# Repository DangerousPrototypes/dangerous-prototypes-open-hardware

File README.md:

# dangerous-prototypes-open-hardware
Automatically exported from code.google.com/p/dangerous-prototypes-open-hardware

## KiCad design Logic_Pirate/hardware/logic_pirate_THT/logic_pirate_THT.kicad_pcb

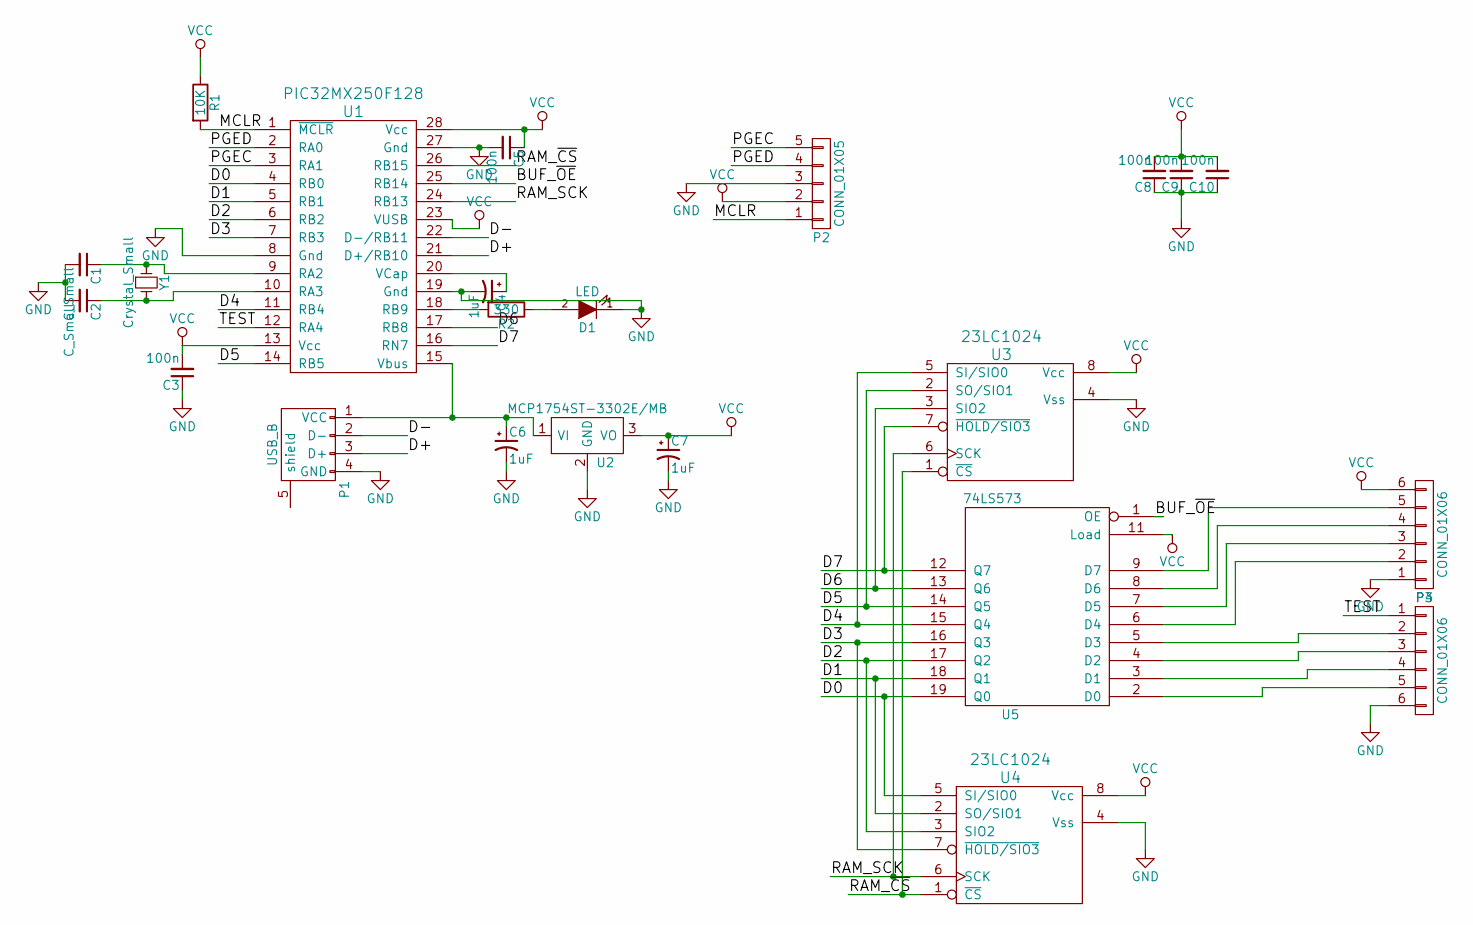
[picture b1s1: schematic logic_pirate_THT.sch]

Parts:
C1, C2: C_Small; C_Disc_D3_P2.5
C3, C5, C8, C9, C10: 100n; C_Disc_D3_P2.5
C4, C6, C7: 1uF; C_Radial_D5_L6_P2.5
D1: LED; LED-5MM
P1: USB_B
P2: CONN_01X05; Pin_Header_Straight_1x05
P3, P4: CONN_01X06; Pin_Header_Straight_1x06
R1: 10K; Resistor_Horizontal_RM10mm
R2: 330; Resistor_Horizontal_RM10mm
U1: PIC32MX250F128; DIP-28_W7.62mm_LongPads
U2: MCP1754ST-3302E/MB; TO-220
U3, U4: 23LC1024; DIP-8_W7.62mm_LongPads
U5: 74LS573; DIP-20_W7.62mm_LongPads
Y1: Crystal_Small; Crystal_HC50-U_Vertical

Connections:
/BUF_~OE: U1.25 (RB14), U5.1 (OE)
/D0: U1.4 (RB0), U4.5 (SI/SIO0), U5.19 (Q0)
/D1: U1.5 (RB1), U4.2 (SO/SIO1), U5.18 (Q1)
/D2: U1.6 (RB2), U4.3 (SIO2), U5.17 (Q2)
/D3: U1.7 (RB3), U4.7 (~HOLD/SIO3), U5.16 (Q3)
/D4: U1.11 (RB4), U3.5 (SI/SIO0), U5.15 (Q4)
/D5: U1.14 (RB5), U3.2 (SO/SIO1), U5.14 (Q5)
/D6: U1.17 (RB8), U3.3 (SIO2), U5.13 (Q6)
/D7: U1.16 (RN7), U3.7 (~HOLD/SIO3), U5.12 (Q7)
/D+: P1.3 (D+), U1.21 (D+/RB10)
/D-: P1.2 (D-), U1.22 (D-/RB11)
/MCLR: P2.1, R1.2, U1.1 (~MCLR)
/PGEC: P2.5, U1.3 (RA1)
/PGED: P2.4, U1.2 (RA0)
/RAM_SCK: U1.24 (RB13), U3.6 (SCK), U4.6 (SCK)
/RAM_~CS: U1.26 (RB15), U3.1 (~CS), U4.1 (~CS)
/TEST: P4.1, U1.12 (RA4)
GND: C1.2, C2.2, C3.1, C4.2, C5.2, C6.2, C7.2, C8.1, C9.1, C10.1, D1.1 (K), P1.4 (GND), P2.3, P3.1, P4.6, U1.8 (Gnd), U1.19 (Gnd), U1.27 (Gnd), U2.2 (GND), U3.4 (Vss), U4.4 (Vss), U5.10 (GND)
unnamed: C1.1, U1.9 (RA2), Y1.1
unnamed: C2.1, U1.10 (RA3), Y1.2
unnamed: C4.1, U1.20 (VCap)
unnamed: C6.1, P1.1 (VCC), U1.15 (Vbus), U2.1 (VI)
unnamed: D1.2 (A), R2.1
unnamed: P3.2, U5.6 (D4)
unnamed: P3.3, U5.7 (D5)
unnamed: P3.4, U5.8 (D6)
unnamed: P3.5, U5.9 (D7)
unnamed: P4.2, U5.5 (D3)
unnamed: P4.3, U5.4 (D2)
unnamed: P4.4, U5.3 (D1)
unnamed: P4.5, U5.2 (D0)
unnamed: R2.2, U1.18 (RB9)
VCC: C3.2, C5.1, C7.1, C8.2, C9.2, C10.2, P2.2, P3.6, R1.1, U1.13 (Vcc), U1.23 (VUSB), U1.28 (Vcc), U2.3 (VO), U3.8 (Vcc), U4.8 (Vcc), U5.11 (Load), U5.20 (VCC)

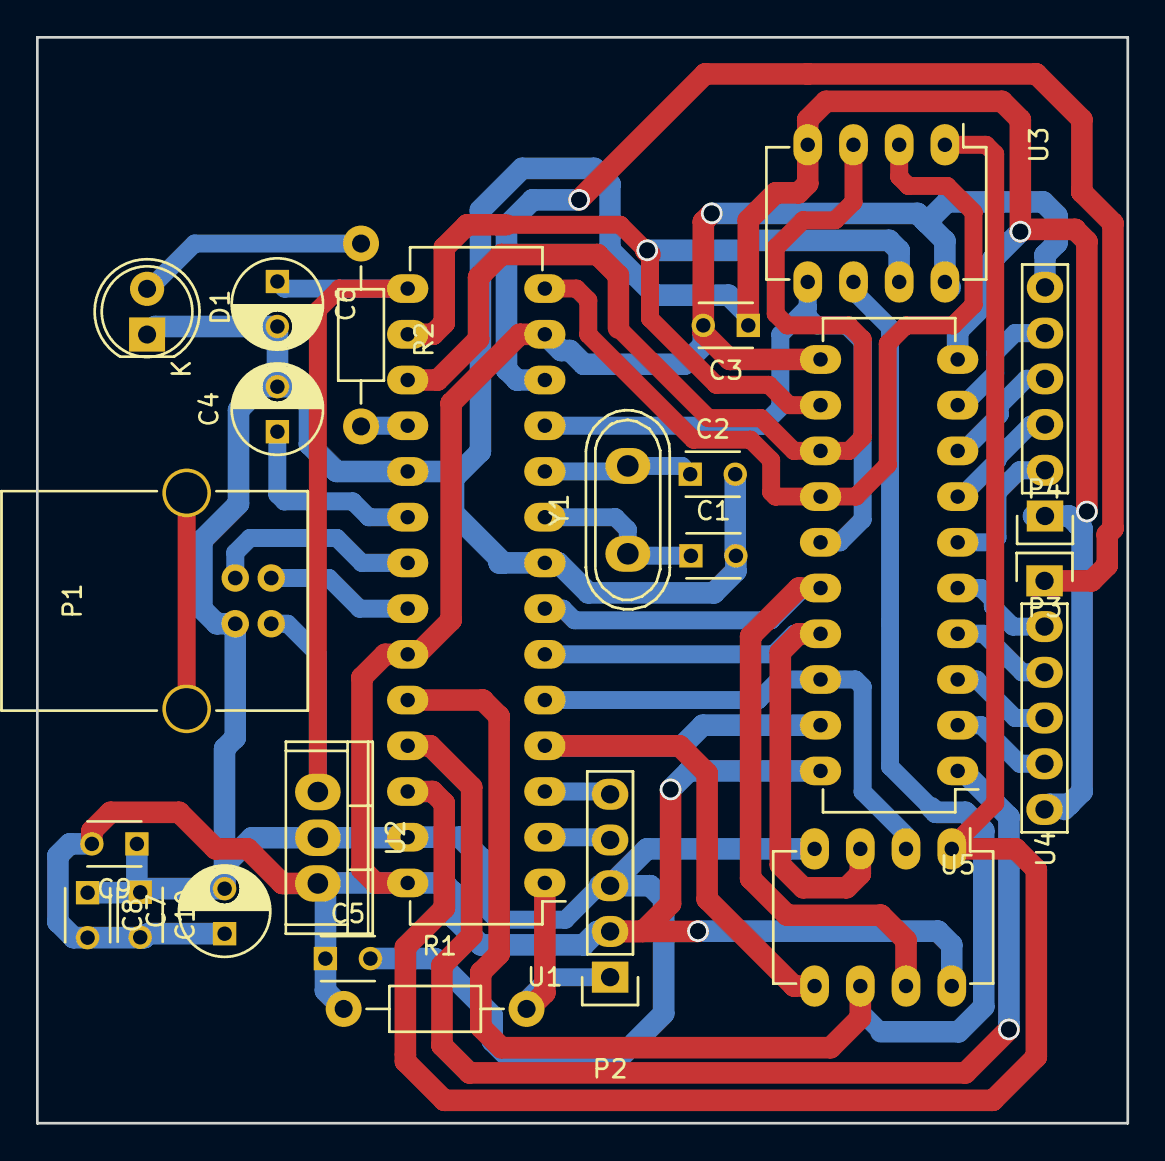
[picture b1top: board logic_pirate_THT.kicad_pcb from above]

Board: 2 copper layers, 60.6 x 60.3 mm, 23 parts (0 on the bottom side), 33 nets.

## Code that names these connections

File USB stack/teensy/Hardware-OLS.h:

/*
*
*	Open Logic Sniffer firmware v1.1
*	http://www.gadgetfactory.net
*	http://dangerousprototypes.com
*	License: GPL
*	Copyright Ian Lesnet 2010
*
*/
#ifndef HARDWARE_PROFILE_H
#define HARDWARE_PROFILE_H

//the first batch of OLS has 20mhz crystal on the PIC
//use this to compile for that hardware
#define XTAL_20MHZ

//hardware version string
#define HW_VER 0x01

//firmware version string
#define FW_VER_H 0x00
#define FW_VER_L 0x06

//Define to enable manufacturing hardware 
//self-test with jumper check on UART header.
//If there is a jumper between RX and TX
//the firmware will light the ACT LED and send 0x03 
//to the FPGA through the UART. THis triggers a test mode
//in special bitstream builds.
#define SELF_TEST	

//measure the voltage on PROG_B (AN3/RA3), should be 2.5volts
#define VREG_TEST
//calculate the ADC value to test for
//#define ADC_2V5 ((25/33)*1024) //2.5volts/3.3volts * 1024 = ADC reading (775.75).
//#define ADC_2V5_LIMIT (ADC_2V5-(ADC_2V5/10)) //show error if not within 10% 775-78=697
#define ADC_2V5_LIMIT 697

//During testing we used a pin for the UART 
// that was sharted with a trigger pin
// some old bitstreams used it and it got confusing
//We had to keep changing it back and forth so I added this define
//There isn't really any reason you should ever need this, 
// especially in the SPI version, but here it is. Enjoy.
//#define OLDRXPIN //use RX on the old pin

//pin setup
/*
A0 PR0 flash_si
A1 PR1 flash_so
A2 flash_cs
A3 PROG_B (pull-down only) test high
A5 RP2 DONE (input only) test high, eventually
C1 RP12 update button (input/interrupt) test high
C2 RP13 ACT LED

B7 RP10 PGD
B6 RP9 PGC
B5 RP8 flash_sck
B4 RP7 FPGA_AUX0
B3 RP6 fpga_cs
B2 RP5 fpga_aux1
B1 RP4 FPGA_AUX2
B0 RP3 FPGA_AUX3
C7 RP18 RX1
C6 RP17 TX1
*/
#define PIN_PROG_B 		PORTAbits.RA3
#define TRIS_PROG_B 	TRISAbits.TRISA3
#define PROG_B_LOW()	PIN_PROG_B=0; TRIS_PROG_B=0 //ground,output
#define PROG_B_HIGH()	PIN_PROG_B=0; TRIS_PROG_B=1	

#define PIN_DONE		PORTAbits.RA5
#define PIN_UPDATE 		PORTCbits.RC1
#define PIN_LED			PORTCbits.RC2

#define TRIS_UART1_TX	TRISCbits.TRISC6
#define PIN_UART1_TX	LATCbits.LATC6
#define TRIS_UART1_RX	TRISCbits.TRISC7
#define PIN_UART1_RX	PORTCbits.RC7
//	#define TRIS_UART1		TRISC
//	#define TXPIN_UART1		0b01000000
//	#define RXPIN_UART1		0b10000000

#define TRIS_UART2_TX	TRISBbits.TRISB1
#define PIN_UART2_TX	PORTBbits.RB1

#define TRIS_FLASH_SCK	TRISBbits.TRISB5
#define PIN_FLASH_SCK	PORTBbits.RB5
#define TRIS_FLASH_MOSI	TRISAbits.TRISA0
#define PIN_FLASH_MOSI	PORTAbits.RA0

#define TRIS_FLASH_CS	TRISAbits.TRISA2
#define PIN_FLASH_CS	PORTAbits.RA2
#define FPGA_CS_LOW()	PIN_FLASH_CS=0; TRIS_FLASH_CS=0
#define FPGA_CS_HIGH() 	PIN_FLASH_CS=1; TRIS_FLASH_CS=0

#define TRIS_FPGA_SCK	TRISBbits.TRISB4
#define PIN_FPGA_SCK	PORTBbits.RB4
#define TRIS_FPGA_MISO	TRISBbits.TRISB2
#define PIN_FPGA_MISO	PORTBbits.RB2
#define TRIS_FPGA_MOSI	TRISBbits.TRISB3
#define PIN_FPGA_MOSI	PORTBbits.RB3
#define TRIS_FPGA_DATAREADY	TRISBbits.TRISB1
#define PIN_FPGA_DATAREADY	PORTBbits.RB1

#define TRIS_FPGA_CS	TRISAbits.TRISA1
#define PIN_FPGA_CS		PORTAbits.RA1

#define BootloaderJump() _asm goto 0x16 _endasm

//these are unneeded, but the stack complains if they're not defined
//#define USE_SELF_POWER_SENSE_IO
#define tris_self_power     TRISCbits.TRISC2    
#define self_power          1

//#define USE_USB_BUS_SENSE_IO
#define tris_usb_bus_sense  TRISCbits.TRISC2    
#define USB_BUS_SENSE       1 

#endif 

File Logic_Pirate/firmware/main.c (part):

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	bool use_trigger;
} config_t;

#define RAM_SCK LATBbits.LATB13
#define SET_RAM_CLOCK_MANUAL ( RPB13Rbits.RPB13R = 0 ) // (PPS) No Connect
#define SET_RAM_CLOCK_REFCLKO ( RPB13Rbits.RPB13R = 7 ) // (PPS) REFCLKO

#define BUF_OE LATBbits.LATB14
#define SET_BUF_ON ( BUF_OE = 0 )
#define SET_BUF_OFF ( BUF_OE = 1 )

#define RAM_CS LATBbits.LATB15
#define SET_RAM_ON ( RAM_CS = 0 )
#define SET_RAM_OFF \
    Nop();          \
    Nop();          \
    Nop();          \
    RAM_CS = 1
// 50 ns nCS hold time.

#define SET_PARALLEL_IN ( TRISB |= 0x01BF )
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    LATBbits.LATB7 = 1;
    uint32_t mask = 1L << ( bit_count - 1 );
    while ( mask != 0 ) {
        RAM_SCK = 0;
        if ( ( data & mask ) != 0 ) {
            LATBbits.LATB0 = 1;
            LATBbits.LATB4 = 1;
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            LATBbits.LATB4 = 0;
        }
        mask >>= 1;
        RAM_SCK = 1;
    }
    RAM_SCK = 0;
    SET_RAM_OFF;
    LATBbits.LATB0 = 0;
    LATBbits.LATB4 = 0;
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    uint32_t nibble_count = 8;
    while ( nibble_count-- > 0 ) {
        const uint8_t nibble = ( data & mask ) >> 28;
        RAM_SCK = 0;
        parallel_write( ( nibble << 4 ) | nibble );
        data <<= 4;
        RAM_SCK = 1;
    }
    RAM_SCK = 0;
    parallel_write( 0x00 );
}

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                               - config->read_count * 2
                               + config->delay_count * 2 ) % 0x1FFFF;
    sqi_write( 0x03000000 | address ); // Read data from memory array beginning at address.
    RAM_SCK = 1; // Dummy Byte
    RAM_SCK = 0;
    RAM_SCK = 1;
    RAM_SCK = 0;
    SET_PARALLEL_IN;

    uint32_t count = config->read_count << 2;
    uint32_t i = 0;
    while ( count > 0 ) {
        --count;
        RAM_SCK = 1;
        USB_In_Buffer[ i++ ] = parallel_read();
        RAM_SCK = 0;
        if ( i >= USB_IN_ENDPOINT_PACKET_SIZE ) {
            i = 0;
            putUSBUSART( USB_In_Buffer, USB_IN_ENDPOINT_PACKET_SIZE );
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    OC4RS = PBCLK / 1000 * 3 / 4; // 75 % duty cycle.
    RPA4Rbits.RPA4R = 5; // (PPS) OC4

    // RAM_SCK pin
    RPB13Rbits.RPB13R = 7; // (PPS) REFCLKO
    REFOCONbits.RODIV = 1; // SYSCLK / ( 2 * 1 ) MHz
    //REFOCONbits.DIVSWEN = 1;
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    SET_RAM_CLOCK_MANUAL;

    // IO
    TRISBbits.TRISB13 = 0; // RAM_SCK
    RAM_SCK = 0;
    TRISBbits.TRISB14 = 0; // BUF_OE
    SET_BUF_OFF;
    TRISBbits.TRISB15 = 0; // RAM_CS
    SET_RAM_OFF;

    SET_PARALLEL_IN;
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
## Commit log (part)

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2012-08-14 Changes to USB interrupt from JTR
2012-08-14 small fix to BPv4 bootloader (comment in wrong place)
    http://dangerousprototypes.com/forum/viewtopic.php?f=28&t=3441&start=45#p42466
2012-08-14 Added USB interrupt fix to BPv4 from: http://dangerousprototypes.com/forum/viewtopic.php?f=28&t=3441&start=45#p42038
2012-08-16 Bus Pirate Demo board firmware
2012-08-20 Added device: 23LC1024 SRAM in SOIC-8
2012-08-27 update to blog theme with header fix, switch for contest theme.
2012-08-27 blog theme contest template update
2012-09-04 Added devices: 74HC595 and 74141 Added footprint: DIL16 Updated: removed extra mounting holes on DP6060 Added schematic symbol: 12V, -12V and -5V Added Logo: Flame logo
2012-09-04 revised credit card sized PCB based on ISO.IEC 7810 ID-1 identification cards sizes, size changed from 85 x 56 mm to 85.60 x 53.98 mm
2012-09-05 SU originals for the ATX case laser cutting
2012-09-06 little file reshuffeling in the ATX laser cutt files
2012-09-07 Fix IN-12 socket, replaced with correct cutout.
2012-09-07 Added: IN-12 Nixie tube display, IN-12 Socket cutout footprint Fixed: IN-12 Socket
2012-09-12 Updated ATX PSU v1.3 Added ATX PSU v2 board. Board was made in KiCAD
2012-09-12 first commit of DP KiCAD part library
2012-09-13 .lib and .mod files converted using eagle2kicad-0.d.ulp from http://www.modulbot.com/download.html Fixed undefined DRAW command when loading to symbol library to KiCAD
2012-09-17 add bus pirate v5c board, enlarge ADC Input label
2012-09-20 Bus Pirate v4 Sick of Beige case laser cutting files and partlist(BOM)
2012-09-21 SoB case generator plugin from Tayken
2012-09-24 Done the changes related to global->instance variables suggested by Jim, corrected some variable name typos and got rid of console debug messages.
2012-09-24 Added new Logic shrimp v2b, this version uses 23LC1024 SRAM
2012-09-25 added direction info on birectional buffer ICs
2012-09-25 Board files
2012-09-25 add schematic image
2012-09-27 OHS 2012 presentations
2012-10-01 Smoke Tester 3D model and renders
2012-10-07 Adding a vertical ATX socket from the Molex MiniFit Jr. line.
    Discrete sockets (key'ed and rectangular) are provided in separate files so they can be easily added to create different configurations. Each socket is made to be "stackable" on both sides, so you'll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
2012-10-07 adding an assortment of 3d models. They should all have origins centered properly about the pins. These were not checked thoroughly, but do appear to be generally correct. Most models are tweaked fro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
    The QFN32 is original and should be extremely easy to scale and accommodate other numbers of pins.
2012-10-08 Added: D8035E VFD board, composed of 3 boards. Board A, B and C
2012-10-08 Added: PTH variant of 2.1mm DC Barrel Connector with milled hole pads
2012-10-09 added series diode on Vusb in and Vin header, moved C8 beside SD holder
2012-10-10 first cut at molex KK series connectors. The 1x2 should be modeled in such a way that it's side stackable, so it will be easy to make additional even numbered connectors. These were based on a model 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
    These should be "close enough" for most purposes, alignment appears to be off a bit on the 4pos header though.
2012-10-10 Bourns TC33X-2-104E 3mm surface mount trim pot
2012-10-10 Added: 3D models for 2 trough-hole IC and a metalized Capacitor.
2012-10-11 added version 2
2012-10-16 rearanged SID SVN, and aded the mauf resources and sales page foleder...as wlell as the sales page txt
2012-10-18 correcting the naming for the 2512 resistor model
2012-10-18 adding a 2010 resistor
2012-10-18 Bus Blaster v4 test buffer project
2012-10-18 Bus blaster v3 v4 manufacturing resrouces
2012-10-22 Soldering Iron Driver renderings and 3D model
2012-10-25 Added projects: DP6037 protoboard v1, DP6037_PTH v1 and DP6037_SMD v1
2012-10-25 add: FT230x_LTC4053_BB
2012-10-25 Add project: FT311 breakout board v1b
2012-10-28 Retrieved demo board v5 files from previous revision, and renamed the wrongly named v5a into proper names
2012-10-30 added DIL-28 PTH to SMD socket
2012-10-31 Added manufacturing files for updated ATX board acrylic case
2012-11-05 added: 4.5 x 4.5 SMD Trimmer, model 3314G
2012-11-07 added right angled 0.1inch 1x06 male header. expanded M1X4, M1X6, M1X8 pads to 1.632mm and drill size to 1.02mm
2012-11-13 added a 1x06 right angled header and a 2x03 SMD straight male headers.
2012-11-15 initial xQFP protoboards folder
2012-11-19 BP v4d, buspirate v4 fitted into a bigger DP PCB (DP7043)
2012-11-22 added ICSP with pogo pin as connector
2012-11-22 fix, ICSP pogo pin programmer footprint by adding a pad on the keyhole for a key pogo pin to be soldered
2012-11-30 added 0.50, 0.65 and 0.80 mm pitch universal QFP footprint and QFP breakout board These footprint are licensed: CC-BY-SA
2012-12-06 added protoboard with 0.50mm xQFP
2012-12-06 added protoboard with 0.65mm and 0.80mm xQFP
2012-12-07 updated 0.5, 0.65 and 0.8 xQFP protoboards by adding a USB footprint. 2-3 SOT-23-6 footprints were removed to fit the usb
2012-12-07 widen pad diameter
2012-12-12 added dual xQFP pitch protoboards, pitch combined are 0.50 + 0.65 mm, 0.80 + 0.50 mm and 0.80 + 0.65 mm. these boards were also having a micro usb footprint under its mini-b footprint
2012-12-12 adding dual pitch back to back footprint on xQFP breakout, combined pitch are 0.50 + 0.65, 0.80 + 0.50 and 0.80 + 0.65 mm QFP
2012-12-14 fix pad, changed via to a pad. new board named v1b
2012-12-20 added: 1x1 PTH hole for protoboard filler changed "board name" of DP standard PCB name(on the bottom) to ">NAME" so it will now be smashable a can be moved around.
2012-12-20 revert back DP Standard PCB with the label name indicating its PCB size
2013-01-07 added 0603 SMD LED, 1x02 and 1x03 right angled 0.1 inch pitched PTH header
2013-01-08 renamed xQFP_protoboard_080_050.v1 to v2
2013-01-10 Bus Pirate - AUXpin.c. Cleaned the code a bit, deleted a huge commented out section, and applyed the patch in issue #65 http://dangerousprototypes.com/track/view.php?id=65
2013-01-11 Bus Pirate firmware -v4 pull up voltage control add to bin protocol. as per issue 63 http://dangerousprototypes.com/track/view.php?id=63 patch available at the link above, and is applied to rev2082
2013-01-14 A slight change in variable definition in procMenu.c, and indent fix in I2C.c
2013-01-16 Bus Pirate firmware issue 51 minor fix to the protos function pointer array, in the BP_USE_I2C section. nulfunc changed to I2Cstop.. http://dangerousprototypes.com/track/view.php?id=51
2013-01-18 HEx files ready for upload through bootloader for BP v3 and v4 6.3r2088
2013-01-22 Bus Pirate firmware - issue 50 added support for RAW mode as well, entered through 'w'
    so now it;s rd foe decimal, rx for HEX, rb for BIN and rw for raw
2013-01-25 Test commit.
2013-01-25 Test
2013-01-25 * Added bootloader.
2013-01-25 * Added bootloadable firmware.
2013-01-26 * Added ZIP packages.
2013-01-27 * Added color scheme for logic shrimp probe cables.
2013-01-31 Bus Pirate Firmware issue #89 - adding UART communications in debugging mode, to activate, #define BPV4_DEBUG, to deactivate comment it out in base.h.. This lets you to connect your debugger and run 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
2013-01-31 * Implemented META command.
2013-02-01 * Improved META command.
2013-02-11 fix ICSP 0.1 inch header pin 5 made it to a circular pad. added proto pads with 1.2mm diameter drills
2013-02-18 add: PTH ferrite bead 10mm pitch, 20x20mm 8x8 LED matrix
2013-02-19 Mark pin 1 of DIP8, DIP14, DIP14W as this is automatically changed to a square pad by DRC check. Corrected SO-8's name and values labels to their proper layers
2013-02-19 Bus blaster v3 manufacturing test package
2013-02-19 update parts list of v3c and v4.1a, copied updated parts list to /hardware folder, made manufacturing resources files for v4.1.
2013-02-21 add BP v3.8 I/O arrangement changed to 5V - GND VPU - 3V3 AUX - ADC MISO - CS MOSI - CLK
2013-03-07 updates on v3.8 USB connector now in micro-B All SMD LEDs are in LED603 IO shrouded header fix, notch is facing outward not much change on the USB D+ D- line just did route them to have almost the sa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
2013-03-07 IO pinout re-arrange to be like bpv4
2013-03-11 Added single pad with 40mil and 32 mil drill size both square and round Added SOIC 14W, 18W, 8NW, 14NW and 16NW footprints N-narrow, W-wide, NW - Narrow + Wide Added 10cm x 10cm (DP100100) in SoB
2013-03-13 change U3 of parts list from a 44 pin to 100 pin XC2C64A-7VQG100C CPLD
2013-03-14 I know the SPI module works with the changes made to the underlying communication tools. However, all the other modules need some verification. I'll probably try to put together some unit-tests. Howe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
2013-03-15 added 24AA04 DIP, 25AA04, MCP3001, MCP4901, MCP9701, TC74 TO220-5 fix some text on POT symbol
2013-03-18 Bus Pirate firmware - commented out #define BPV4_DEBUG so it's in normal mode by default
2013-04-03 Added: MCP4131 Digital Potentiometer Tester Probe socket QFN 12 and 16 pins 3x3cm QFN 16, 20 and 24 4x4 cm SOIC Narrow+Wide 18, 20, 24 and 28 pins
2013-04-16 Added board files
2013-04-23 added gerbmerge config creator ULP
2013-04-26 fix project multiple default to zero when project multiple spinbox is not touched
2013-05-08 moved anchor/reference point of SoB PCBs to its center
2013-06-23 * Updated version info.
2013-06-25 * Improved USB command parsing.
2013-07-23 Added: MCP7940 I2C RTC with SRAM in SOIC8 and DIP8, Alternate 3 Pins Voltage Regulator to accomodate 4th pin as tab connection. Revised VREG 3 PINS now with TO-220 Horizontal footprint
2013-07-24 bus pirate: fix slashes and filename case for linux compatibility
2013-09-28 merging PyBusPirateLite branch back into mainline
2014-01-10 changed SMD SMC-A pad size from 1.60 x 1.40 to 1.40 x 1.80 changed SMD SMC-B pad size from 1.60 x 2.40 to 1.40 x 2.80 added new SMD SMC-C footprint added part MBI5026 (SOIC-24 variant) 16-Bit constan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
2014-02-03 Stepper motor driver based on Linistepper v2.0 (http://www.romanblack.com/lini.htm)
2014-02-11 SMD Tape cutting controller intended to automatically dispense SMD parts
2014-02-11 wrong folder
2014-02-11 uploaded directories and files
2014-02-23 SPI mode } command was giving errors, busPirateCore.c line 225 now maps to SPIstop for stopR. Should fix it. Untested.
2014-03-21 correct EEPROM for v2/2.5, v3c and v4a, old EEPROM value was non 3.3V compliant (93C46), replaced with 93LC46B. updated schematic, wiki, BOM/Partlist. Board and gerbers still the same
2014-03-23 changed VR1, VR2 LDO regulators to MCP1801T-3302I/OT and VR3 to MCP1801T-5002I/OT. to fix the issue on LDO output voltage oscillation due to the usage of ceramic caps on the output of each LDO. these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
2014-08-22 Fix for http://dangerousprototypes.com/forum/viewtopic.php?f=4&t=6667
2014-08-28 added bus pirate v3.8a a compact bus pirate v3.8 fitted within 5x5cm SoB board
2014-08-29 -added library for version 6, keeping older version as is for older kicad users
2014-09-03 board update: -changed ICSP header to 6pins, spare pin not connected -moved all LEDs a little to the right for even space
2014-09-03 committing initial files
2014-09-04 -fix the overlapping resistors (R2 and LCD SMT voltage dividers resistors)
2014-11-04 various parts added
2015-08-28 Migrating wiki contents from Google Code
2017-04-30 Fix rescue lib
2017-05-15 Update for python3
    Now the script detects whether it is being executed under python 3.X or python 2.X.
2019-09-15 @makaveli344
    Deep quantum time machine xpapi
